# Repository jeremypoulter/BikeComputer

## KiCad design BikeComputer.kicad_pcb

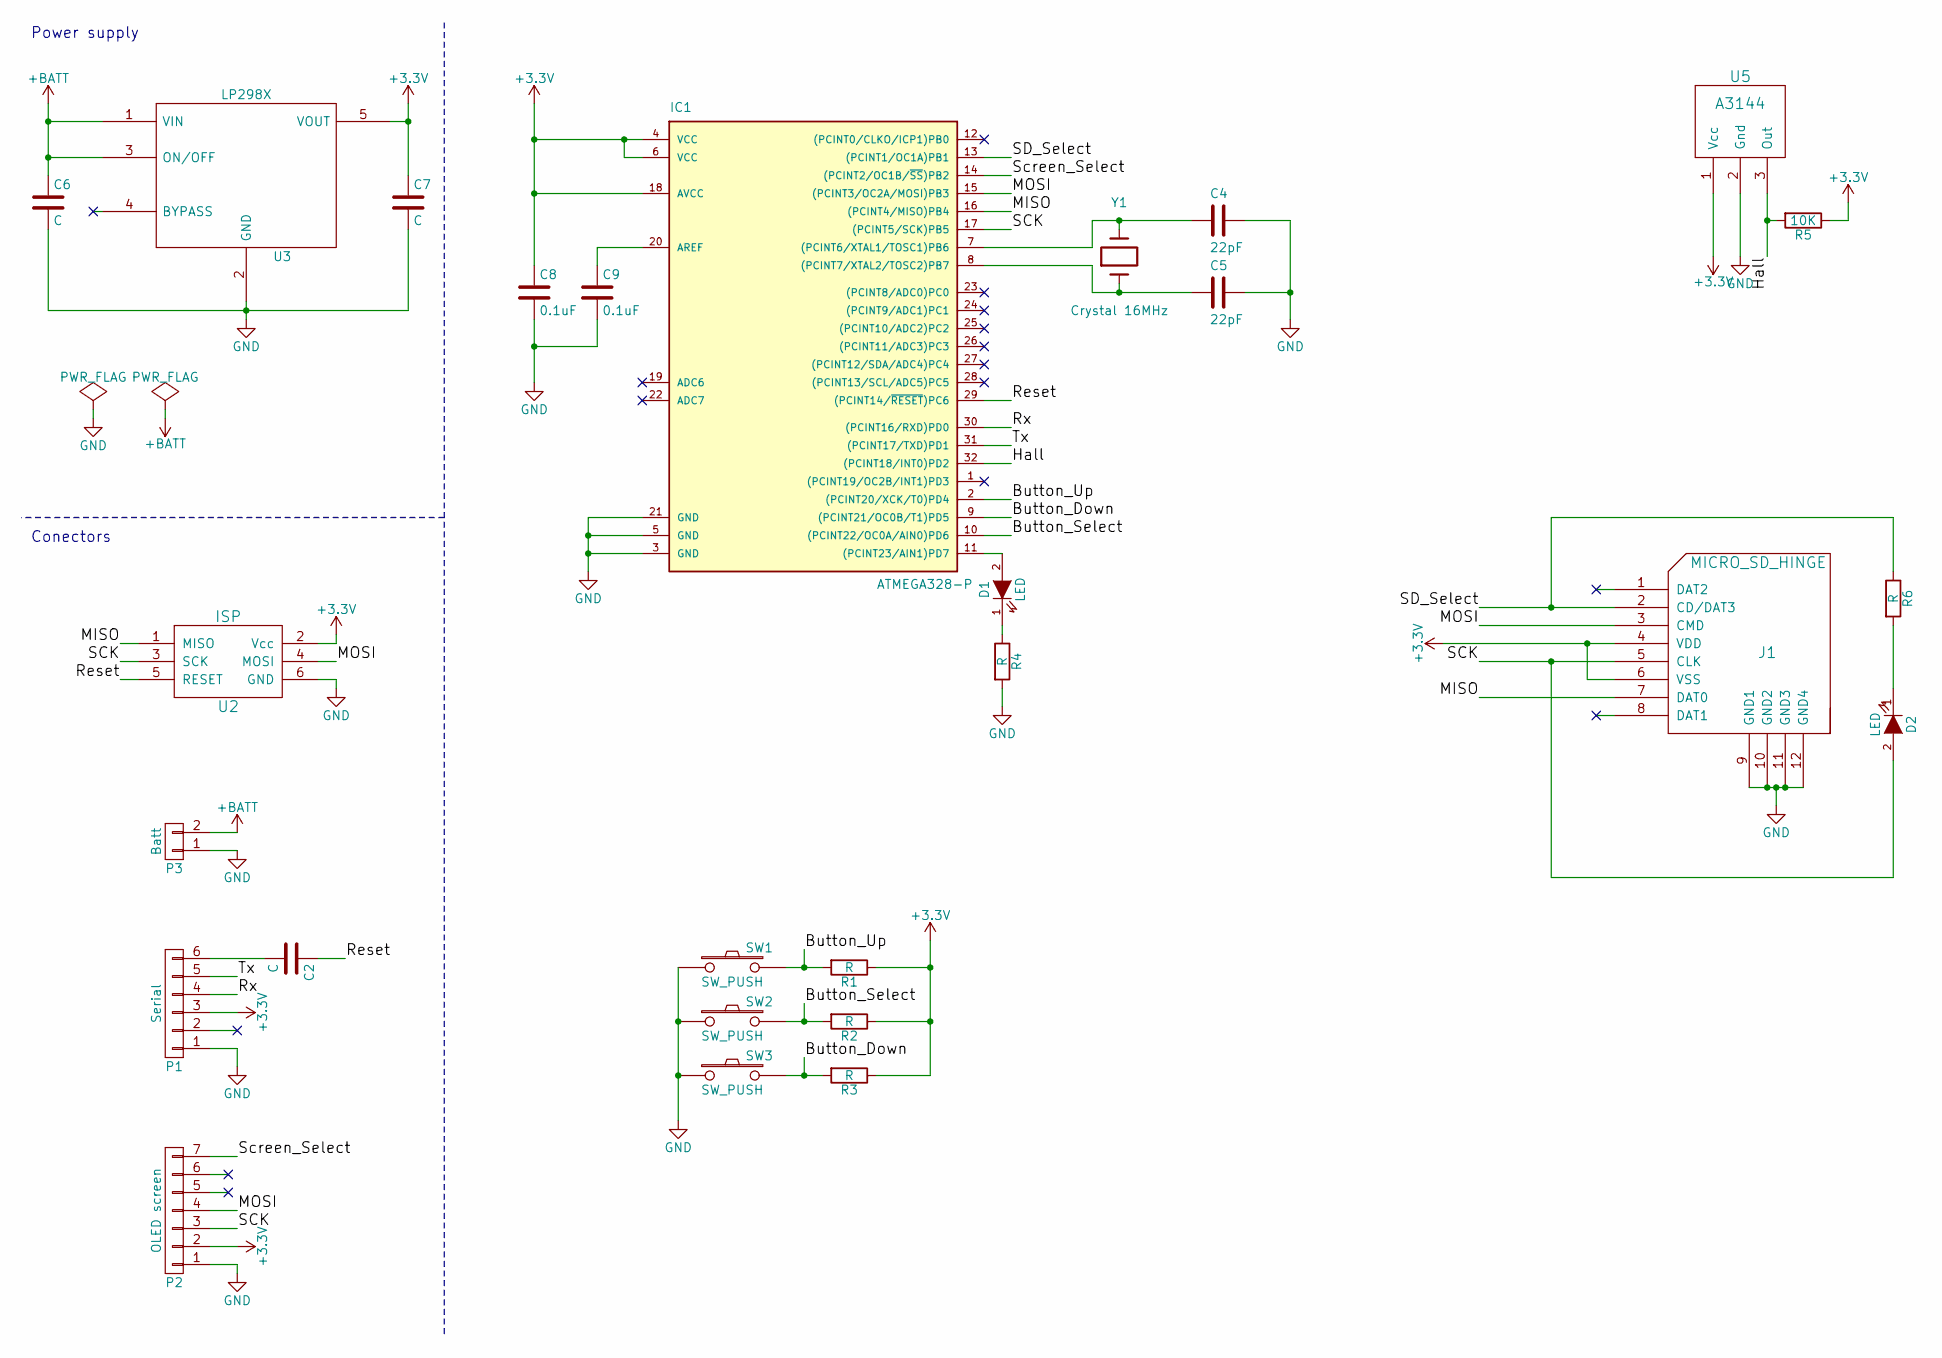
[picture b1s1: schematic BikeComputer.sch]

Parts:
C2, C6, C7: C; C_0603_HandSoldering
C4, C5: 22pF; C_0603_HandSoldering
C8, C9: 0.1uF; C_0603_HandSoldering
D1, D2: LED; LED_0603
IC1: ATMEGA328-P; TQFP-32_7x7mm_Pitch0.8mm
J1: MICRO_SD_HINGE
P1: Serial; Pin_Header_Straight_1x06
P2: OLED screen; Socket_Strip_Straight_1x07
P3: Batt; Pin_Header_Straight_1x02
R1, R2, R3, R4, R6: R; R_0603_HandSoldering
R5: 10K; R_0603_HandSoldering
SW1, SW2, SW3: SW_PUSH
U2: ISP; Pin_Header_Straight_2x03
U3: LP298X; SOT-23-5
U5: A3144; Pin_Header_Straight_1x03
Y1: Crystal 16MHz; Crystal_HC50-U_Vertical

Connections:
+3V3: C7.1, C8.1, IC1.4 (VCC), IC1.6 (VCC), IC1.18 (AVCC), J1.4 (VDD), J1.6 (VSS), P1.3, P2.2, R1.1, R2.1, R3.1, R5.1, U2.2 (Vcc), U3.5 (VOUT), U5.1 (Vcc)
+BATT: C6.1, P3.2, U3.1 (VIN), U3.3 (ON/OFF)
/Button_Down: IC1.9 ((PCINT21/OC0B/T1)PD5), R3.2, SW3.2
/Button_Select: IC1.10 ((PCINT22/OC0A/AIN0)PD6), R2.2, SW2.2
/Button_Up: IC1.2 ((PCINT20/XCK/T0)PD4), R1.2, SW1.2
/Hall: IC1.32 ((PCINT18/INT0)PD2), R5.2, U5.3 (Out)
/MISO: IC1.16 ((PCINT4/MISO)PB4), J1.7 (DAT0), U2.1 (MISO)
/MOSI: IC1.15 ((PCINT3/OC2A/MOSI)PB3), J1.3 (CMD), P2.4, U2.4 (MOSI)
/Reset: C2.1, IC1.29 ((PCINT14/~RESET~)PC6), U2.5 (RESET)
/Rx: IC1.30 ((PCINT16/RXD)PD0), P1.4
/SCK: D2.2 (A), IC1.17 ((PCINT5/SCK)PB5), J1.5 (CLK), P2.3, U2.3 (SCK)
/SD_Select: IC1.13 ((PCINT1/OC1A)PB1), J1.2 (CD/DAT3), R6.1
/Screen_Select: IC1.14 ((PCINT2/OC1B/~SS~)PB2), P2.7
/Tx: IC1.31 ((PCINT17/TXD)PD1), P1.5
GND: C4.1, C5.1, C6.2, C7.2, C8.2, C9.2, IC1.3 (GND), IC1.5 (GND), IC1.21 (GND), J1.9 (GND1), J1.10 (GND2), J1.11 (GND3), J1.12 (GND4), P1.1, P2.1, P3.1, R4.2, SW1.1, SW2.1, SW3.1, U2.6 (GND), U3.2 (GND), U5.2 (Gnd)
unnamed: C2.2, P1.6
unnamed: C4.2, IC1.7 ((PCINT6/XTAL1/TOSC1)PB6), Y1.2
unnamed: C5.2, IC1.8 ((PCINT7/XTAL2/TOSC2)PB7), Y1.1
unnamed: C9.1, IC1.20 (AREF)
unnamed: D1.1 (K), R4.1
unnamed: D1.2 (A), IC1.11 ((PCINT23/AIN1)PD7)
unnamed: D2.1 (K), R6.2

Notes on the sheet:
Power supply
Conectors

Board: 2 copper layers, 26 parts (0 on the bottom side), 22 nets, no tracks yet.

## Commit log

2016-08-24 Assigned footprints and started on PCB
2016-08-24 Changed to use the TQFP version of the 328P
    Added a battery connector
    Moved over to use 3.3v only as all bar the hall sensor are 3.3v capable. TODO find a replacement hall sensor that is 3.3v.
